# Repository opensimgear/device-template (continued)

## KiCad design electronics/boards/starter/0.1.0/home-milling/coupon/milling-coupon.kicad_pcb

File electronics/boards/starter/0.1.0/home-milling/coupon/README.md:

# Two-layer milling qualification coupon

## Development status and disclaimer

This project is heavily under development and is not ready for use. Use it entirely at your own risk. To the fullest extent permitted by applicable law, the authors and contributors disclaim all liability for any damage, loss, or other issues arising from its use.

This **45 × 35 mm coupon** tests whether the proposed home PCB milling process can reproduce the device-template's smallest features. It is an unpowered geometry and hand-assembly test, **not a working USB circuit, a device PCB, or an impedance test**. No milling toolpaths, machine settings, Gerbers or fabrication order have been created.

Open `milling-coupon.kicad_pro` in KiCad 10, or review [the copper PDF](review/coupon.pdf), [front SVG](review/front.svg) and [back SVG](review/back.svg). The back preview uses top-down coordinates viewed through the board, rather than a mirrored milling setup. Gray `F.Fab` graphics and labels describe the tests; they are not copper and are not intended to be milled. Red/blue preview features are front/back copper; the black holes are NPTH drill features.

## Areas and geometry

Coordinates below are KiCad millimetres. The outline runs from `(100,100)` to `(145,135)`.

| Area | Test |
| --- | --- |
| Upper left, J1 centred `(112,108)`, rotated 180° | Actual stock `Connector_USB:USB_C_Receptacle_GCT_USB4105-xx-A_16P_TopMnt_Horizontal` footprint. Four independent 0.20 mm fanout traces on the fine-pitch contacts, ending at separate probe lands. |
| Upper right, U1 centred `(133,109)` | Actual stock `Package_QFP:LQFP-48_7x7mm_P0.5mm` footprint. Four left-edge and six lower-edge pads have 0.20 mm fanouts with width-matched probe lands. |
| Right middle, U2 centred `(140.5,117.5)` | Exact `OpenSimGear:TI_DCK0006A_SC70-6_LM66100` footprint for LM66100DCKR, with **0.65 mm pitch / 0.90 × 0.40 mm rounded lands / 0.25 mm adjacent pad gap**. All six contacts have separate 0.20 mm fanouts and 0.50 × 0.20 mm probe lands, ending at x=138 mm on the left or x=143.4 mm on the right. |
| Bottom left/middle | Three columns for **0.20 / 0.25 / 0.30 mm edge gaps**. Each column has paired 8 mm tracks of **0.20 / 0.25 / 0.30 / 0.40 mm width**, top to bottom. Every width/gap combination is present. Narrow end lands preserve each nominal gap. |
| Bottom right, WV1 and WV2 | Four **0.80 mm drill / 1.80 mm diameter double-sided lands**, centred at `(138,123)`, `(141,123)`, `(138,128)`, `(141,128)`. Two front bridges join each row; separate back protrusions provide probe access. |
| Diagonal corners | Two **2.00 mm NPTH alignment holes** centred at `(102.5,102.5)` and `(142.5,132.5)`, 50 mm apart. These are registration test features; machine fixture design and flipping procedure remain to be established. |

The stock LQFP and fine USB contacts have **0.50 mm pitch, 0.30 mm copper pad width and 0.20 mm nominal interpad gap**. Passing only the 0.25 or 0.30 mm track-gap columns is insufficient: the actual device footprints still require the narrower gap. Tool diameter, tip wear, runout, cutting depth, material flatness and alignment affect the achievable isolated channel; establish these from the test, not a nominal tool label. A wider effective isolation cutter cannot reproduce a narrower channel.

The SC70 area reproduces the actual manufacturer-derived lands used by the device's LM66100 power-source selectors, including their rounded corners and pin numbering. Its 0.25 mm pad gap and six independent probe connections add a separate isolation/solderability test. Use the [TI DCK0006A drawing in the LM66100 datasheet](https://www.ti.com/lit/ds/symlink/lm66100.pdf) when checking an actual part; this area has no power-selection circuit and must remain unpowered.

The unmodified USB footprint also has **0.65 mm locating holes, 0.60 mm-wide elongated shell slots**, and approximately **0.194 mm closest pad-to-locating-hole clearance**. Test these alongside fine-pitch isolation. The custom project records a 0.15 mm hole-to-copper minimum to accommodate this stock geometry; that CAD rule is not a promise of milling accuracy. The separate 0.80 mm wire holes do not replace the connector's smaller mechanical holes or slots.

## No plating or soldermask assumptions

The WV holes are represented by KiCad through-hole pads to display their copper lands on both faces and connect the design model. A **milled board has no plated barrel**: the two faces remain physically separate until a wire or suitable rivet is installed and joined on **both faces**. Solder both sides in the accessible WV area, then test front-to-back continuity and inspect for lifted copper. Do not infer real electrical continuity from the CAD model's automatic PTH connection.

The same absence of plating applies to the USB shell lands. This coupon supplies no circuit, no ground plane and no power. USB fine contacts are independent geometry tests; D+ and D− duplicate contacts are intentionally not joined. Shell pads are unassigned. Optional test-fitting of an actual connector or MCU should assess mechanical alignment and solderability only. There is no electrical reason to attach a cable or power supply.

The home process does not depend on soldermask. Keep exposed adjacent lands clear of solder bridges. On the real device a wire-via layout must also give access to both sides of every manually joined transition; this small coupon cannot establish that accessibility for a denser device layout.

## Record a pass before adapting the device

Use the [qualification record](qualification-record.md) to record the actual machine process and measurements.

1. Measure the surviving copper widths and isolated gaps across all twelve lane pairs; inspect the actual QFP/USB/SC70 pad rows and fanouts under magnification for bridges, torn pads and burrs. Include SC70's 0.25 mm pad gaps and rounded land edges.
2. Confirm continuity along each individual lane and each of the six SC70 pad-to-probe paths, and isolation between different nets. Keep the inspection tool's resolution and observed process variation in the test record.
3. Drill/test the alignment holes, flip using the intended fixture, and measure front/back registration at the four WV lands. Check remaining annulus around every drilled hole rather than assuming the two sides aligned.
4. Install wire/rivet connections in WV1/WV2 and solder both sides. Verify back-probe to front-bridge continuity and that neither row shorts to the other. Check slot and locating-hole fit for the selected USB connector.
5. Record laminate thickness, copper weight, milling/isolation method, effective tool width/depth, fixture/registration procedure, measured feature sizes and which tests failed. Use those measured limits to set the separate home-device board rules.

A successful coupon qualifies the tested process geometries and accessible wire joins. It does not qualify USB impedance, USB electrical compliance, the full device's component footprints, or all assembly access. If the narrow pad row fails, investigate the process or use a different assembly/breakout strategy before milling the compact device board.

## CAD checks and reproduction

KiCad **10.0.6** all-track DRC, refreshed **2026-10-12 with the SC70 area fitted**, reports **0 violations and 0 unconnected items**; see [the saved report](review/drc.rpt). Checks include minimum 0.20 mm track width / copper clearance, 0.50 mm edge clearance and 0.15 mm hole-to-copper clearance. No custom DRC exclusions were added. Ignored check categories remain listed in the report. There is no schematic and no schematic-parity claim. Connectivity checks use KiCad's plated through-hole model and do not verify physical wire joints.

The source `.kicad_pcb` embeds the stock USB/QFP and exact authored SC70 footprints. `OpenSimGear.pretty/` and the project-relative `fp-lib-table` keep the SC70 footprint available for editing; no other working layout is a dependency. `geometry.json` records nominal dimensions and all six SC70 pad/probe coordinates. `make_coupon.py` reproduces the source using the Python bundled with KiCad on this Mac; it reads installed upstream footprints plus the coupon's local SC70 footprint, and adjusts the included standalone project settings. Set `KICAD10_FOOTPRINT_DIR` if your upstream library lives elsewhere. Run the script from any directory; outputs remain beside it. The editable coupon files and previews are sufficient for review without regeneration. Upstream KiCad library data retains [its license](LICENSE-KICAD.md). The separately authored SC70 footprint is copyright © Ivan Gregurić Ortolan, all rights reserved while licensing is under review; see the repository [temporary licensing policy](../../../../../../LICENSE) and [contribution policy](../../../../../../CONTRIBUTING.md).

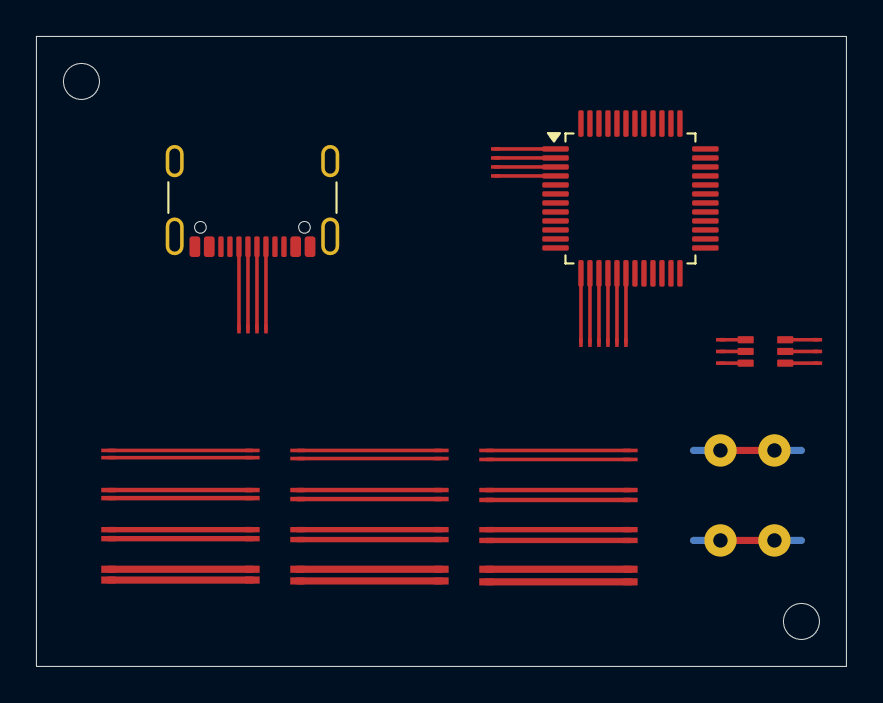
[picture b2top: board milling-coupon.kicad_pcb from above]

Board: 2 copper layers, 45.0 x 35.0 mm, 33 parts (0 on the bottom side), 50 nets.

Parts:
A1, A2: 2 mm NPTH alignment; MountingHole_2mm
BACK_END_L0, BACK_END_L1: probe end
BACK_END_R0, BACK_END_R1: probe end
G1: gap 0.20
G2: gap 0.25
G3: gap 0.30
J1: USB4105-GF-A milling fit test; USB_C_Receptacle_GCT_USB4105-xx-A_16P_TopMnt_Horizontal
QFP_END_1, QFP_END_2, QFP_END_3, QFP_END_4, QFP_END_13, QFP_END_14, QFP_END_15, QFP_END_16, QFP_END_17, QFP_END_18: probe end
SC70_END_1, SC70_END_2, SC70_END_3, SC70_END_4, SC70_END_5, SC70_END_6: probe end
U1: LQFP48 milling fit test; LQFP-48_7x7mm_P0.5mm
U2: LM66100DCKR milling fit test; TI_DCK0006A_SC70-6_LM66100
USB_END_A6, USB_END_A7: probe end
USB_END_B6, USB_END_B7: probe end
WV: manual wire vias

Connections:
G200_W200_A: G1.A0L, G1.A0R
G200_W200_B: G1.B0L, G1.B0R
G200_W250_A: G1.A1L, G1.A1R
G200_W250_B: G1.B1L, G1.B1R
G200_W300_A: G1.A2L, G1.A2R
G200_W300_B: G1.B2L, G1.B2R
G200_W400_A: G1.A3L, G1.A3R
G200_W400_B: G1.B3L, G1.B3R
G250_W200_A: G2.A0L, G2.A0R
G250_W200_B: G2.B0L, G2.B0R
G250_W250_A: G2.A1L, G2.A1R
G250_W250_B: G2.B1L, G2.B1R
G250_W300_A: G2.A2L, G2.A2R
G250_W300_B: G2.B2L, G2.B2R
G250_W400_A: G2.A3L, G2.A3R
G250_W400_B: G2.B3L, G2.B3R
G300_W200_A: G3.A0L, G3.A0R
G300_W200_B: G3.B0L, G3.B0R
G300_W250_A: G3.A1L, G3.A1R
G300_W250_B: G3.B1L, G3.B1R
G300_W300_A: G3.A2L, G3.A2R
G300_W300_B: G3.B2L, G3.B2R
G300_W400_A: G3.A3L, G3.A3R
G300_W400_B: G3.B3L, G3.B3R
MANUAL_WIRE_1: BACK_END_L0.1, BACK_END_R0.1, WV.1, WV.2
MANUAL_WIRE_2: BACK_END_L1.1, BACK_END_R1.1, WV.3, WV.4
QFP_PAD_1: QFP_END_1.1, U1.1
QFP_PAD_2: QFP_END_2.1, U1.2
QFP_PAD_3: QFP_END_3.1, U1.3
QFP_PAD_4: QFP_END_4.1, U1.4
QFP_PAD_13: QFP_END_13.1, U1.13
QFP_PAD_14: QFP_END_14.1, U1.14
QFP_PAD_15: QFP_END_15.1, U1.15
QFP_PAD_16: QFP_END_16.1, U1.16
QFP_PAD_17: QFP_END_17.1, U1.17
QFP_PAD_18: QFP_END_18.1, U1.18
SC70_PAD_1: SC70_END_1.1, U2.1
SC70_PAD_2: SC70_END_2.1, U2.2
SC70_PAD_3: SC70_END_3.1, U2.3
SC70_PAD_4: SC70_END_4.1, U2.4
SC70_PAD_5: SC70_END_5.1, U2.5
SC70_PAD_6: SC70_END_6.1, U2.6
USB_CONTACT_A1: J1.A1, J1.B12
USB_CONTACT_A4: J1.A4, J1.B9
USB_CONTACT_A6: J1.A6, USB_END_A6.1
USB_CONTACT_A7: J1.A7, USB_END_A7.1
USB_CONTACT_A9: J1.A9, J1.B4
USB_CONTACT_A12: J1.A12, J1.B1
USB_CONTACT_B6: J1.B6, USB_END_B6.1
USB_CONTACT_B7: J1.B7, USB_END_B7.1
